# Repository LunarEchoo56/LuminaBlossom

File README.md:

# LuminaBlossom — Wi-Fi-Controlled Lotus Light

*Finished physical build: the illuminated blossom, diffuser and wooden base.*

LuminaBlossom is an interactive ambient light built around a **Raspberry Pi Pico 2 W** and a **16-pixel RGBW NeoPixel ring**, housed in a laser-cut wooden base beneath a decorative lotus blossom. It hosts a local web interface for lighting patterns, custom animations and guided breathing meditations. Control it from a browser on your local network—no companion app or cloud account is required.

## What it does and why it exists

The project combines handcrafted decorative art with programmable light. Instead of being a fixed-colour lamp, LuminaBlossom can change its colours and animation in response to settings you choose, or guide a breathing exercise with coordinated light. Its Wi-Fi setup flow is designed to make the device usable from a phone, tablet or computer without installing an app.

## What you can do

- **Control it in a browser:** after joining your Wi-Fi network, open `http://luminablossom.local` on a device on the same LAN.
- **Create light patterns:** adjust colour, brightness, pulse, flicker, sparkle and other animation settings.
- **Save and reuse presets:** store named animation configurations on the device.
- **Run guided meditations:** use a breathing exercise with matching light transitions.
- **Provision Wi-Fi locally:** first-time setup uses the device's `LuminaBlossom_Setup` access point.
- **Keep the project hackable:** firmware, browser pages, enclosure cutting patterns and assembly instructions are included.

## Photos, electronics and manufacturing references

### Finished hardware and assembly

*Assembly photo showing the Pico 2 W and wiring before the case is closed.*

*Cut wooden layers before final assembly.*

### What the browser interface looks like

*Feature overview: web control panel alongside the project's printed instructions.*

### Wiring reference

*Connection diagram for the build described in this repository. The Pico, LED ring and level shifter must share a ground.*

### LED ring PCB component

*The off-the-shelf NeoPixel ring used as a component reference. This is **not** a custom LuminaBlossom PCB.*

### Laser-cut source preview

*This is a preview of the 2D cutting/engraving layout, not a 3D CAD model.*

## Hardware design files: what is actually included

The enclosure design files already exist in the repository:

- **[Laser-cut SVG source](enclosure/luminablossom.svg)** — editable 2D vector paths for the wooden base/spindle parts. It can be imported into compatible laser-cutting software.
- **[xTool Studio source project](enclosure/luminablossom.xs)** — native xTool project file for use with xTool Studio.
- **[Enclosure file notes](enclosure/README.md)** — intended material, file descriptions and licensing.
- **[Illustrated assembly guide](docs/assembly.md)** — dimensions/material notes, photos and build sequence.

### KiCad carrier PCB and 3D model status

A new **Rev A draft carrier/interconnect PCB** is included under [`hardware/kicad/`](hardware/kicad/README.md). It plugs the existing Pico 2 W into two socket rows and adds a through-hole SN74AHCT125N level shifter, 330 Ω data resistor, 100 nF bypass capacitor, 470 µF bulk capacitor, and a 3-pin LED output header.

*Illustrative preview generated from the native board source; not a physical board photo or KiCad screenshot.*

*Quick connection overview; the native KiCad schematic remains the source of truth.*

- [Native PCB layout](hardware/kicad/luminablossom_carrier.kicad_pcb)
- [Native schematic](hardware/kicad/luminablossom_carrier.kicad_sch)
- [KiCad project settings](hardware/kicad/luminablossom_carrier.kicad_pro)
- [Pin mapping and manufacturing notes](hardware/kicad/README.md)

**This PCB is a prototype draft, not a fabrication-ready design.** KiCad ERC/DRC has not been run here, and the board has not been fabricated or physically tested. Review connector orientation, exact footprints, USB clearance, board outline and routing in KiCad before ordering. Gerber and drill files are not included until validation is complete.

The board is a carrier, not a custom NeoPixel-ring PCB. The enclosure remains the existing laser-cut 2D design in [SVG](enclosure/luminablossom.svg) and [xTool Studio](enclosure/luminablossom.xs) formats. There is no Fusion 360, STEP/STP or STL model in the repository.

## Wiring

The firmware sends LED data on **GP16 (physical Pico pin 21)**. Use a 5 V-compatible logic buffer such as a 74AHCT125 between the Pico's 3.3 V GPIO output and the NeoPixel ring's data input. The code comment in `src/led_controller.cpp` assumes a level shifter is present.

| Connection | Destination |
|---|---|
| Pico pin 40 (`VBUS`, 5 V from USB) | NeoPixel ring `5V` and level-shifter `VCC` |
| Pico pin 38 (`GND`) | NeoPixel `GND` and level-shifter `GND` |
| Pico GP16 (physical pin 21) | Level-shifter input |
| Level-shifter output | NeoPixel ring `DIN` |
| Level-shifter active-low `/OE` | `GND` |

Use one channel of the 74AHCT125 and check the exact component/package pinout before wiring. Keep the data path short and connect all grounds together. The default firmware caps LED brightness at 20%; verify the USB supply and wiring before increasing brightness.

## How to assemble

1. **Check the parts and patterns.** Review the [BOM below](#bill-of-materials) and the [enclosure notes](enclosure/README.md). The pictured enclosure uses 3 mm birch plywood; check scale and kerf on your laser cutter before cutting the full set.
2. **Cut the wooden parts.** Use [`enclosure/luminablossom.svg`](enclosure/luminablossom.svg) with compatible cutting software, or [`enclosure/luminablossom.xs`](enclosure/luminablossom.xs) with xTool Studio. Validate laser power, speed and scale on scrap material.
3. **Build and finish the case.** Glue the wooden layers into the top and bottom assemblies, sand/stain/finish as desired, and let finishes cure before fitting electronics.
4. **Prepare the blossom and diffuser.** Fit the decorative lotus piece and cabochon/diffuser to the spindle arrangement, then route the three LED leads through the base as described in the [full assembly guide](docs/assembly.md).
5. **Wire the electronics.** Connect ring power and ground, and route GP16 through a 5 V logic buffer to the ring's data input. Confirm pin labels and continuity before powering it.
6. **Close the case.** Secure the Pico, check that no wire is pinched, fit the screws and rubber feet, then connect USB power.

Use the [full illustrated assembly guide](docs/assembly.md) for the detailed procedure, photos and safety notes. Laser cutting, soldering and drilling require suitable ventilation, eye protection and secure workholding.

## Build and flash the firmware

The project uses PlatformIO with the Arduino framework for Pico 2 W (Earle Philhower Arduino-Pico core).

1. Install VS Code and the PlatformIO extension, then open this repository as a project.
2. Use a **data-capable Micro-USB cable** to connect a Raspberry Pi Pico **2 W** (not the non-wireless Pico 2).
3. Build the firmware:

   ```sh
   pio run
   ```

4. Upload the filesystem from the `data/` folder:

   ```sh
   pio run --target uploadfs
   ```

5. Upload the firmware:

   ```sh
   pio run --target upload
   ```

If the board is not detected for the first upload, hold **BOOTSEL** while connecting USB, then retry. When both code and `data/` files have changed, upload the filesystem first and the firmware second. See the [build and upload guide](docs/build_and_upload.md) for detailed instructions.

### First-time Wi-Fi setup

On first boot, connect a phone or computer to the `LuminaBlossom_Setup` Wi-Fi access point and follow the provisioning page to enter your home Wi-Fi details. Once the device has joined the network, open `http://luminablossom.local` from a device on the same local network. Some networks or operating systems do not resolve `.local` hostnames reliably; use the IP address printed in the serial monitor if needed.

## Known issues and practical notes

- **Pico 2 W matters:** the standard Pico 2 has no Wi-Fi radio, so it cannot provide the same network features.
- **LED data voltage:** GP16 is 3.3 V logic while the NeoPixel ring is powered at 5 V. Use a 74AHCT125 or equivalent buffer for reliable signal levels; do not assume a direct wire will work with every ring.
- **Power and brightness:** the firmware brightness cap is 20%. Check the USB supply and wiring before raising it or displaying all channels at full intensity.
- **Filesystem updates:** changes under `data/` require `pio run --target uploadfs`; uploading only the firmware does not update those files.
- **Local hostname:** `luminablossom.local` depends on mDNS support on the client network. Check the serial monitor for the device IP if hostname resolution fails.
- **Carrier PCB is a draft:** KiCad source is included, but ERC/DRC, mechanical fit and physical validation are outstanding. No Gerber/drill files are published yet. The enclosure remains 2D laser-cut; no Fusion, STEP/STP or STL file is included.

## Credits and licences

- The hardware uses a [Raspberry Pi Pico 2 W](https://www.raspberrypi.com/documentation/microcontrollers/raspberry-pi-pico.html) and an [Adafruit 16-pixel RGBW NeoPixel ring](https://www.adafruit.com/product/2854).
- The [74AHCT125 level shifter](https://www.adafruit.com/product/1787) is listed as the reference option for translating 3.3 V logic to the ring's 5 V data level.
- The Fredoka and Gluten font licence notices are available as [Fredoka OFL](data/fonts/FredokaOFL.txt) and [Gluten OFL](data/fonts/Gluten_OFL.txt).
- **Software:** Apache License 2.0; see [LICENSE](LICENSE).
- **Enclosure vector design:** Creative Commons Attribution 4.0 International (CC BY 4.0); see [enclosure/README.md](enclosure/README.md). Component vendor pages and third-party assets remain subject to their own terms.

## Bill of Materials

The root-level [`BOM.csv`](BOM.csv) contains the same parts list in spreadsheet-friendly form. Supplier links are examples to help identify parts; availability, pricing and regional alternatives may change. The logic-level shifter is included because the firmware's wiring notes assume one.

| Part | Qty. | Example link | Notes |
|---|---:|---|---|
| Raspberry Pi Pico 2 W | 1 | [Adafruit](https://www.adafruit.com/product/6087) · [Raspberry Pi documentation](https://www.raspberrypi.com/documentation/microcontrollers/raspberry-pi-pico.html) | Must be the wireless **2 W** model. |
| 16-pixel RGBW NeoPixel ring (SK6812) | 1 | [Adafruit](https://www.adafruit.com/product/2854) | Preassembled LED ring PCB; connect 5 V, ground and data input. |
| SN74AHCT125N DIP-14 buffer IC | 1 | [TI datasheet](https://www.ti.com/lit/ds/symlink/sn74ahct125.pdf) | Through-hole IC used on the carrier PCB. |
| 330 Ω through-hole resistor | 1 | General component | Series resistor between buffer output and LED DIN. |
| 100 nF ceramic capacitor | 1 | General component | Supply bypass capacitor near U1. |
| 470 µF / 10 V electrolytic capacitor | 1 | General component | Bulk capacitor near LED output; observe polarity. |
| Female 1×20 socket strip, 2.54 mm | 2 | General component | Two Pico socket rows; nominal row spacing 17.78 mm. |
| Male 1×3 header, 2.54 mm | 1 | General component | Output pins: 5 V, GND, LED DIN. |
| Two-layer carrier PCB | 1 | [KiCad source](hardware/kicad/luminablossom_carrier.kicad_pcb) | Draft only; not DRC-validated or fabricated. |
| Capiz-shell lotus tealight holder or compatible decorative blossom | 1 | [Example design](https://www.worldmarket.com/p/capiz-20-petal-lotus-tealight-candle-holder-119956.html) | Decorative part; substitute a compatible piece as needed. |
| 50 mm frosted-glass cabochon or translucent diffuser | 1 | [Example](https://www.amazon.com/dp/B07JKZP1Z6) | A translucent acrylic disc can also work. |
| 3 mm basswood or birch plywood | About 8 × 12 in | Local craft/lumber supplier | For the laser-cut base; confirm actual pattern scale and material. |
| Micro-USB data cable | 1 | [Example](https://www.amazon.com/Charging-Transfer-Android-Trustable-MYFON/dp/B098DW7485/) | Must support data for firmware uploads. |
| 5 V USB power adapter, 1 A or suitably rated | 1 | [Example](https://www.amazon.com/Certified-Charger-Universal-Portable-Adapter/dp/B017TXGM4I/) | Ensure the adapter/cable can safely supply the Pico and LEDs at your selected brightness. |
| M2 screws, 6 mm | 4 | [Amazon example](https://www.amazon.com/HVAZI-Metric-Notebook-Computer-Assortment/dp/B075C6C4YR/) · [McMaster-Carr](https://www.mcmaster.com/91698A202/) | To mount the Pico to the wooden base. |
| #6 wood screws, 1/2 in | 3 | [Amazon example](https://www.amazon.com/TPOHH-Stainless-Phillips-Threaded-5x12SS18-8/dp/B092Q87W39/) · [McMaster-Carr](https://www.mcmaster.com/90031A552/) | To fasten the enclosure halves. |
| Self-adhesive rubber feet | 3 | [Adafruit](https://www.adafruit.com/product/550) · [Amazon example](https://www.amazon.com/dp/B074PXFWPK) | Cover the screw heads and keep the base from slipping. |
| Wood glue, solder and finishing materials | As needed | Local hardware/craft supplier | Assembly consumables; stain, Danish oil and hot glue are optional finishes/adhesives. |

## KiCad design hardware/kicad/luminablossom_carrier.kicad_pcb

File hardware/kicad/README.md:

# LuminaBlossom KiCad carrier (Rev A draft)

This is a **new carrier / interconnect PCB** for the existing LuminaBlossom architecture. It is not a custom NeoPixel ring board and is not claimed to be fabricated or tested.

## Files

- `luminablossom_carrier.kicad_pro` — KiCad project settings.
- `luminablossom_carrier.kicad_sch` — editable schematic with cached symbols.
- `luminablossom_carrier.kicad_pcb` — editable two-layer board layout with nets and routed connections.
- `board_preview.svg` — illustrative preview generated from the draft board source, not a KiCad screenshot.
- `schematic_preview.svg` — quick wiring overview; the native schematic is the source of truth.

## Board contents

- J1/J2: two 1×20 female socket strips for the Pico 2 W, with 17.78 mm row spacing.
- U1: SN74AHCT125N through-hole DIP-14 buffer.
- R1: 330 Ω series resistor between the buffer output and LED DIN.
- C1: 100 nF bypass capacitor at U1.
- C2: 470 µF / 10 V radial bulk capacitor near the LED output. Confirm polarity.
- J3: 1×3 output header, pad 1 = +5 V, pad 2 = GND, pad 3 = buffered LED DIN.

## Electrical notes

- GP16 is physical Pico pin 21 and provides 3.3 V logic. U1 is powered from +5 V to translate the signal to a 5 V data level.
- Pico physical pin 40 (VBUS) supplies the +5 V rail in this draft; all grounds must be common.
- U1 uses gate 1 for the data path. Unused inputs are held low; unused active-low output enables are held high.
- A 330 Ω series resistor and 470 µF bulk capacitor are included as practical interface components. Confirm actual ring requirements and USB supply capacity.

## Before manufacturing

**Do not order this Rev A draft without review.** Open the project in KiCad 9 and:

1. Check the Pico socket orientation and spacing against the exact module; check USB connector clearance and actual enclosure fit.
2. Confirm footprints match the exact socket strips, DIP-14 IC, resistor, capacitors, and 1×3 header.
3. Run schematic ERC and PCB DRC. Resolve errors and inspect silkscreen/courtyard overlaps.
4. Confirm the SN74AHCT125N pinout, J3 pin order, capacitor polarity and supply path against datasheets.
5. Only after validation, export Gerber and drill files. No Gerber/Excellon outputs are included yet.

## Validation status

KiCad CLI was not available in the authoring environment. The files have been checked for balanced source delimiters and obvious different-net route intersections, but a KiCad load, ERC, DRC, fabrication and physical test are **not** claimed. The project’s original enclosure is a 2D laser-cut design; no Fusion 360, STEP or STL model is included.

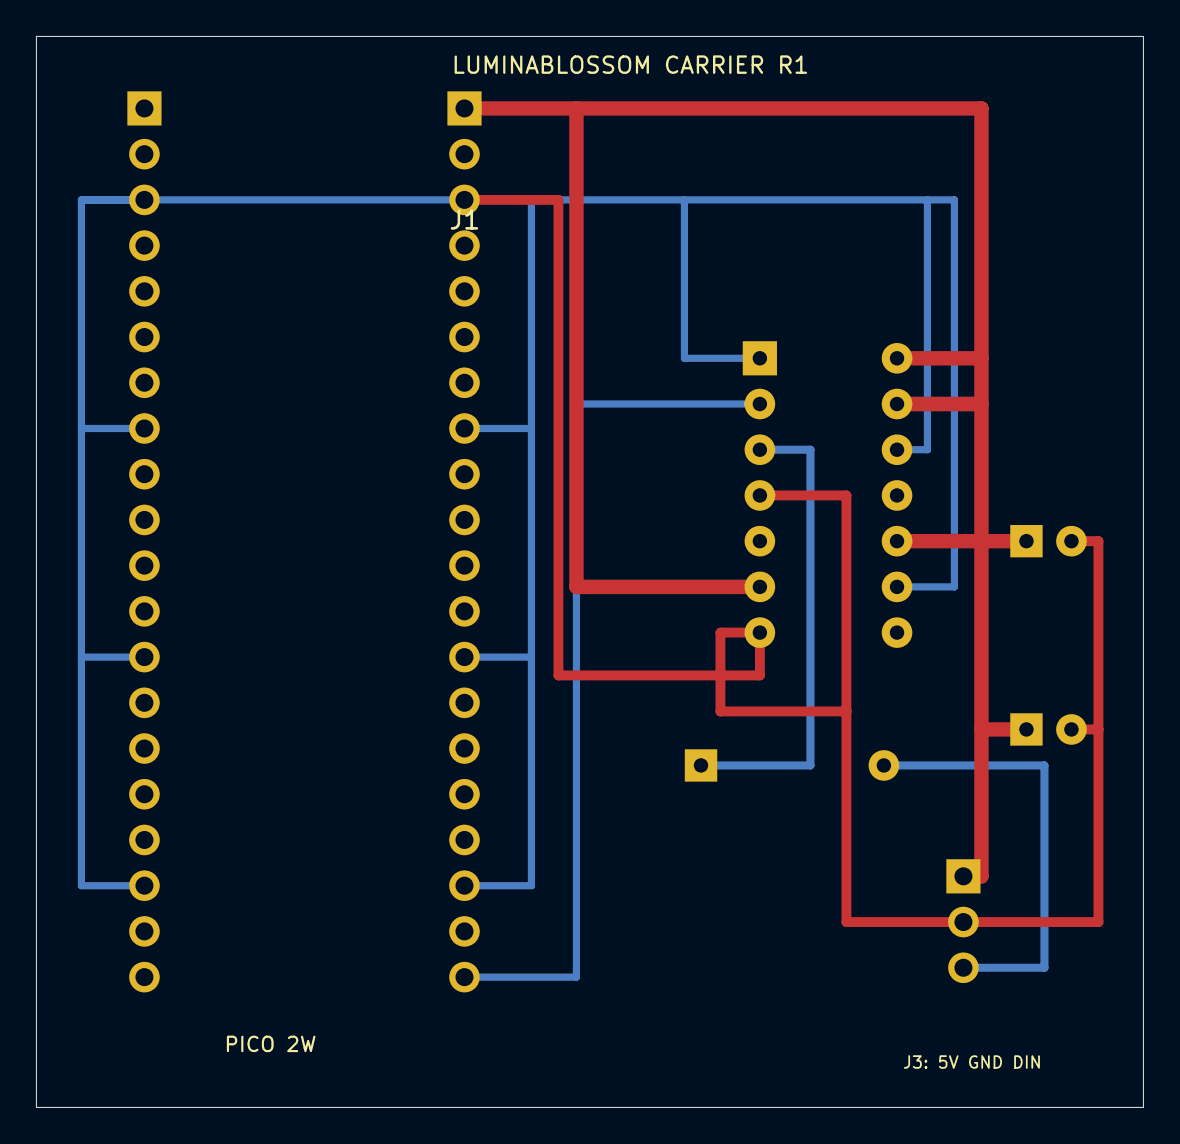
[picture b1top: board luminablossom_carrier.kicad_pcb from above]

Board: 2 copper layers, 61.5 x 59.5 mm, 7 parts (0 on the bottom side), 5 nets.

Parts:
C1: 100nF; C_Disc_D5.0mm_W2.5mm_P2.50mm
C2: 470uF 10V; CP_Radial_D6.3mm_P2.50mm
J1: Pico left pins 1-20; PinSocket_1x20_P2.54mm_Vertical
J2: Pico right pins 40-21; PinSocket_1x20_P2.54mm_Vertical
J3: 5V GND DIN; PinHeader_1x03_P2.54mm_Vertical
R1: 330R; R_Axial_DIN0207_L6.3mm_D2.5mm_P10.16mm_Horizontal
U1: SN74AHCT125N; DIP-14_W7.62mm

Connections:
+5V: C1.1 (+), C2.1 (+), J2.1 (VBUS), J3.1 (+5V), U1.6 (/2OE), U1.10 (/3OE), U1.13 (/4OE), U1.14 (VCC)
GND: C1.2 (-), C2.2 (-), J1.3 (GND), J1.8 (GND), J1.13 (GND), J1.18 (GND), J2.3 (GND), J2.8 (GND), J2.13 (GND), J2.18 (GND), J3.2 (GND), U1.1 (/1OE), U1.4 (2A), U1.7 (GND), U1.9 (3A), U1.12 (4A)
LED_DATA_3V3: J2.20 (GP16), U1.2 (1A)
LED_DATA_5V: J3.3 (LED_DIN), R1.2 (B)
LED_DATA_BUF: R1.1 (A), U1.3 (1Y)

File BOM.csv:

Item,Component,Quantity,Specification / Notes,Example Supplier URL(s)
1,"Raspberry Pi Pico 2 W",1,"Wi-Fi-capable controller; the non-wireless Pico 2 is not a substitute for network features.","https://www.adafruit.com/product/6087; https://www.raspberrypi.com/documentation/microcontrollers/r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"
2,"16-pixel RGBW NeoPixel ring (SK6812)",1,"Preassembled LED ring PCB; connect 5 V, ground and data input.","https://www.adafruit.com/product/2854"
3,"SN74AHCT125N buffer IC",1,"Through-hole DIP-14 on the new carrier PCB; confirm package pinout. Gate 1 buffers GP16 and unused gates have defined input/enable states.","https://www.ti.com/lit/ds/symlink/sn74ahct125.pdf"
4,"Capiz-shell lotus tealight holder or compatible decorative blossom",1,"Decorative part; substitute a compatible holder if the pictured style is unavailable.","https://www.worldmarket.com/p/capiz-20-petal-lotus-tealight-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"
5,"50 mm frosted-glass cabochon or translucent diffuser",1,"A translucent acrylic disc is an alternative.","https://www.amazon.com/dp/B07JKZP1Z6"
6,"3 mm basswood or birch plywood","About 8 x 12 in","For the laser-cut base; confirm actual pattern scale and material before cutting.","Local craft/lumber supplier"
7,"Micro-USB data cable",1,"Must support data for firmware uploads.","https://www.amazon.com/Charging-Transfer-Android-Trustable-M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"
8,"5 V USB power adapter","1; 1 A or suitably rated","Ensure the adapter/cable can supply the Pico and LEDs at the selected brightness.","https://www.amazon.com/Certified-Charger-Universal-Portable-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"
9,"M2 screws, 6 mm",4,"For mounting the Pico to the wooden base.","https://www.amazon.com/HVAZI-Metric-Notebook-Computer-Assort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; https://www.mcmaster.com/91698A202/"
10,"#6 wood screws, 1/2 in",3,"For fastening the enclosure halves.","https://www.amazon.com/TPOHH-Stainless-Phillips-Threaded-5x1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; https://www.mcmaster.com/90031A552/"
11,"Self-adhesive rubber feet",3,"Cover the screw heads and prevent slipping.","https://www.adafruit.com/product/550; https://www.amazon.com/dp/B074PXFWPK"
12,"Wood glue, solder and finishing materials","As needed","Assembly consumables; stain, Danish oil and hot glue depend on the chosen finish.","Local hardware/craft supplier"
13,"Custom two-layer carrier PCB",1,"Rev A draft, nominal outline 61.5 x 59.5 mm. Source is included; no manufacturing files are released until DRC and mechanical fit are reviewed.","hardware/kicad/luminablossom_carrier.kicad_pcb"
14,"Female 1x20 socket strip, 2.54 mm pitch",2,"Two rows receive the Pico 2 W; nominal row spacing 17.78 mm. Check actual module and headers.","Generic electronic components supplier"
15,"330 ohm axial through-hole resistor",1,"R1 series resistor between the 74AHCT125 output and LED DIN. Draft footprint DIN0207, 10.16 mm pitch.","General electronic components supplier"
16,"100 nF ceramic capacitor, 2.5 mm lead pitch",1,"C1 bypass capacitor placed near U1 supply pins.","General electronic components supplier"
17,"470 uF, 10 V radial electrolytic capacitor, 2.5 mm pitch",1,"C2 bulk capacitor near the LED output. Observe polarity and check physical body clearance.","General electronic components supplier"
18,"Male 1x3 header, 2.54 mm pitch",1,"J3 LED output connector: pin 1=+5 V, pin 2=GND, pin 3=LED DIN.","General electronic components supplier"
